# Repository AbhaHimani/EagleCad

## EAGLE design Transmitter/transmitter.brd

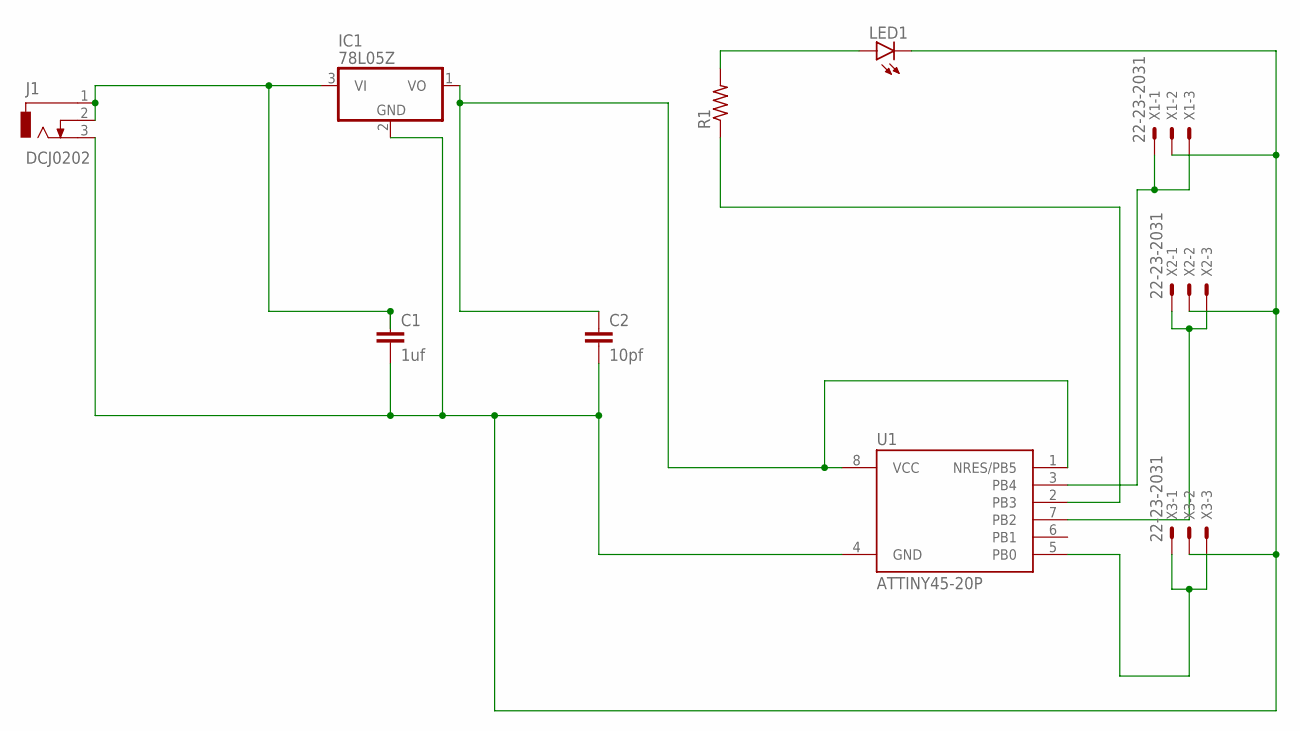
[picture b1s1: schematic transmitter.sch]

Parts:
C1: 1uf; C2.5-2
C2: 10pf; C2.5-2
IC1: 78L05Z; TO92
J1: DCJ0202
LED1: LED3MM
R1: R-US_0207/10; 0207/10
U1: ATTINY45-20P; PDIP08_300MIL
X1, X2, X3: 22-23-2031

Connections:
unnamed: C1.1, IC1.3 (VI), J1.1, J1.2
unnamed: C1.2, C2.2, IC1.2 (GND), J1.3, LED1.K (C), U1.4 (GND), X1.2, X2.2, X3.2
unnamed: C2.1, IC1.1 (VO), U1.1 (NRES/PB5), U1.8 (VCC)
unnamed: R1.1, U1.2 (PB3)
unnamed: LED1.A, R1.2
unnamed: U1.3 (PB4), X1.1, X1.3
unnamed: U1.7 (PB2), X2.1, X2.3
unnamed: U1.5 (PB0), X3.1, X3.3

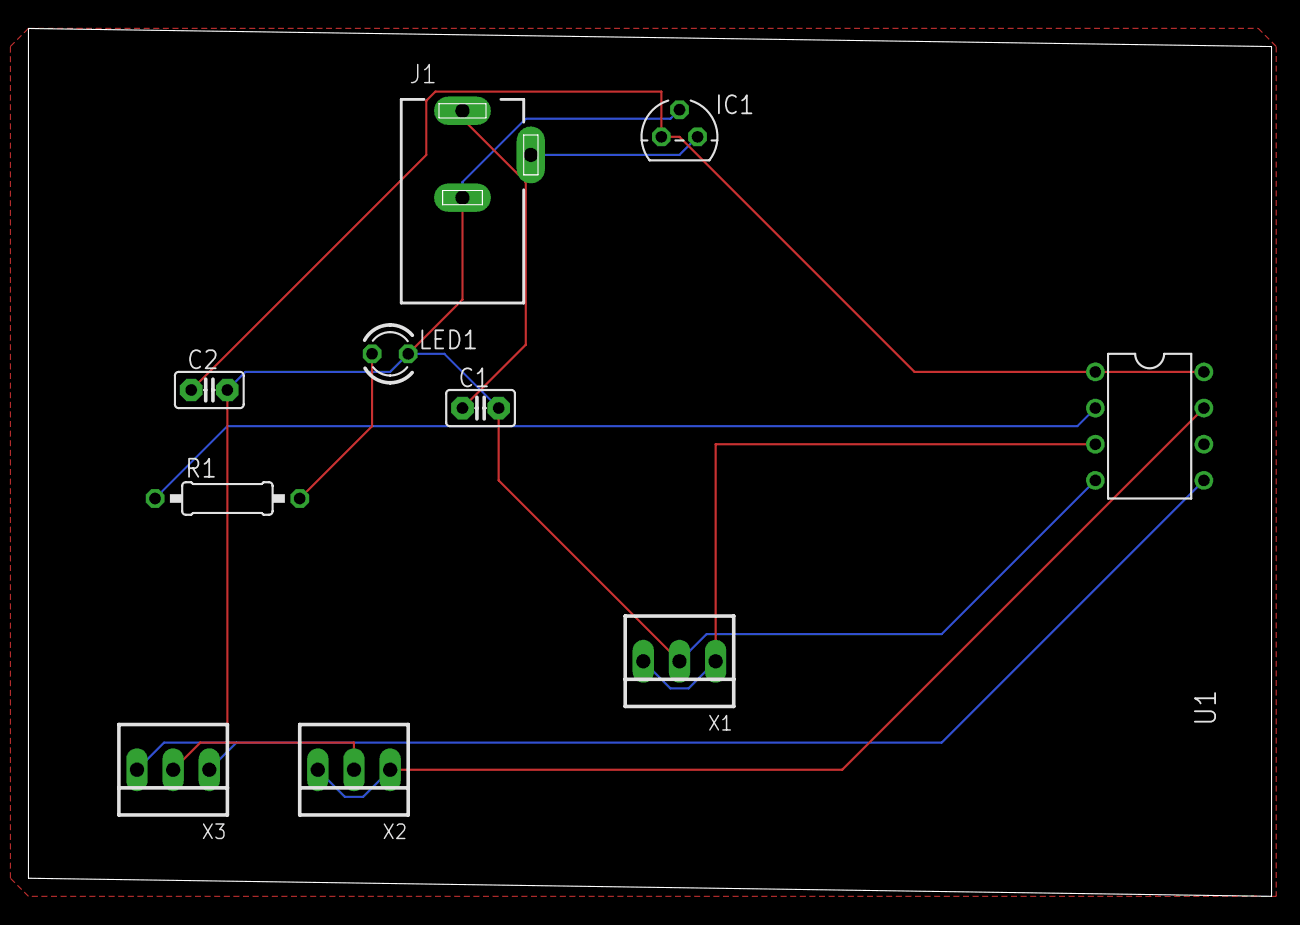
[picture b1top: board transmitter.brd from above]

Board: 2 copper layers, 87.3 x 61.0 mm, 10 parts (0 on the bottom side), 8 nets.

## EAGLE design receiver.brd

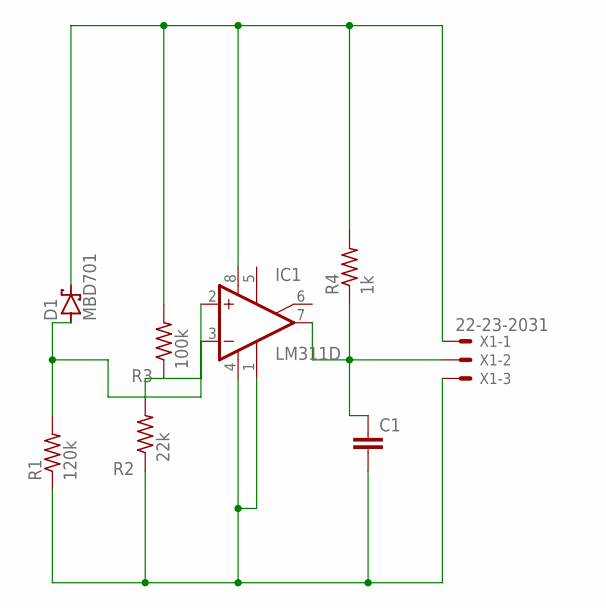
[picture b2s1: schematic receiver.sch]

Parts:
C1: C2.5/2; C2.5-2
D1: MBD701; TO92H
IC1: LM311D; SO08
R1: 120k; 0207/10
R2: 22k; 0207/10
R3: 100k; 0207/10
R4: 1k; 0207/10
X1: 22-23-2031

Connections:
unnamed: D1.2 (C), IC1.8 (V+), R3.2, R4.2, X1.1
unnamed: C1.2, IC1.1 (GND), IC1.4 (V-), R1.1, R2.1, X1.3
unnamed: D1.1 (A), IC1.2 (+IN), R1.2
unnamed: IC1.3 (-IN), R2.2, R3.1
unnamed: C1.1, IC1.7 (OUT), R4.1, X1.2

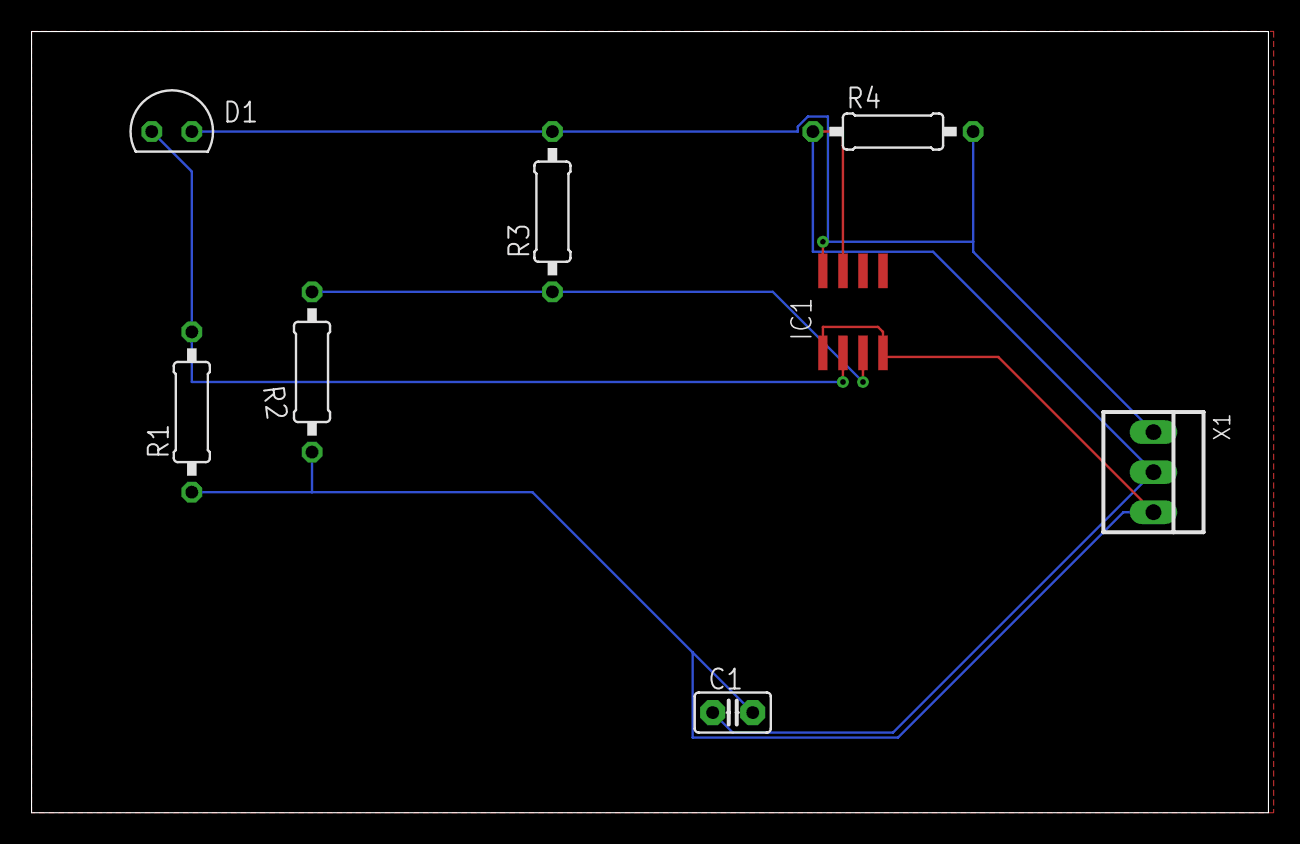
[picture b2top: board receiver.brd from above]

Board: 2 copper layers, 78.4 x 49.5 mm, 8 parts (0 on the bottom side), 5 nets.

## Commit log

2022-03-07 Receiver
